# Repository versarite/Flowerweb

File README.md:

# FlowerWeb
# Written with support from ChatGPT and Claude

A small web-controlled watering system for a Raspberry Pi. Open the web page from anywhere (for example over Tailscale), watch your plants on a live camera, water them with one click, or let a timer do it every 24, 48 or 72 hours.

The server is written in Free Pascal / Lazarus and runs as a systemd service. The camera stream is served by [MediaMTX](https://github.com/bluenviron/mediamtx).

## Features

- **Manual watering:** opens the valve for a set time (1–60 s by default)
- **Automatic watering:** every 24, 48 or 72 hours. The schedule survives restarts, and a watering missed while the Pi was off runs when it comes back.
- **Live camera:** a WebRTC stream from a USB webcam or the Raspberry Pi camera
- **Status:** shows the Pi's IP address, CPU temperature, next watering time and a countdown while watering
- **Remote reboot** from the web page
- **Safe valve handling:** the valve is closed at startup, at shutdown, when the service crashes and before a reboot, and the server enforces a maximum opening time

## Hardware

| Part | Notes |
|---|---|
| Raspberry Pi | Any model with GPIO. Uses `pinctrl` (Pi 5 / Bookworm) or `raspi-gpio` (older models) |
| Relay module | Signal on **GPIO 18** by default. Active-high and active-low boards are both supported (`ActiveLow` in the ini) |
| Water valve or pump | Switched by the relay. Use a separate power supply that suits the valve |
| Camera | USB webcam (`/dev/video0`) or Raspberry Pi camera module |

A ready-made **Raspberry Pi HAT** for all of this is in [`hardware/kicad`](hardware/kicad/README.md). It has a 5 V 6 A input jack, a 24 V step-up module, a TIP121 valve driver on GPIO 18, a 24 V valve jack and a status-LED header.

> ⚠️ The relay switches the valve's supply, not mains power. If your valve or pump runs on mains voltage, use a suitably rated relay and have the wiring checked by someone qualified.

The KiCAD hat board meant as a suggestion. No frills here, only GPIO18 is connected.   

## Project layout

```
flowerweb/
├── src/        Pascal source (Lazarus project flowerweb.lpi)
│   ├── flowerweb.lpr   program start, HTTP routes
│   ├── uconfig.pas     reads/writes config/flowerweb.ini
│   ├── uRelay.pas      valve control and watering timer
│   ├── uapi.pas        REST API
│   ├── uwebfiles.pas   serves the web page
│   ├── usysinfo.pas    CPU temperature and IP address
│   └── ulog.pas        logging
├── web/        index.html, app.js, style.css
├── config/     flowerweb.ini, mediamtx.yml (USB camera), mediamtx.yml_rpicam (Pi camera)
├── systemd/    flowerweb.service, mediamtx.service
├── scripts/    deploy.sh (build and install on the Pi), reset.sh (Wi-Fi watchdog)
├── hardware/   kicad/: FlowerWeb HAT schematic, board layout and BOM (see its README)
└── docs/       notes and command reference
```

On the Pi everything lives in `/home/flowerweb`, and the compiled program goes in `/home/flowerweb/bin`.

## Installation on the Raspberry Pi

1. **Install Lazarus** (for `lazbuild`) and create the folders:

   ```bash
   sudo apt install lazarus
   sudo mkdir -p /home/flowerweb/bin
   sudo chown -R pi:pi /home/flowerweb
   ```

2. **Install MediaMTX** for the camera. Download the ARM build from the [MediaMTX releases](https://github.com/bluenviron/mediamtx/releases) and put `mediamtx` in `/home/flowerweb/bin`. Copy the config that matches your camera:

   ```bash
   cp config/mediamtx.yml        /home/flowerweb/bin/mediamtx.yml   # USB webcam (needs ffmpeg)
   # or
   cp config/mediamtx.yml_rpicam /home/flowerweb/bin/mediamtx.yml   # Pi camera module
   ```

3. **Allow the service commands without a password** (`sudo visudo -f /etc/sudoers.d/flowerweb`):

   ```
   pi ALL=(root) NOPASSWD: /usr/sbin/reboot, /usr/bin/systemctl
   ```

4. **Install the services:**

   ```bash
   sudo cp /home/flowerweb/systemd/*.service /etc/systemd/system/
   sudo systemctl daemon-reload
   sudo systemctl enable --now mediamtx flowerweb
   ```

## Building and deploying

Development happens on a PC. `scripts/deploy.sh` copies the source to the Pi over SSH, compiles it there with `lazbuild`, installs it and restarts the service:

```bash
./scripts/deploy.sh
```

Set `PI_HOST` in the script to your Pi's address. Password-free SSH login is described in `docs/`.

### Testing without touching the live system

```bash
./scripts/deploy-test.sh          # copy, compile and start a test copy on port 8081
./scripts/deploy-test.sh log      # follow its log
./scripts/deploy-test.sh stop     # stop it
```

The test copy runs from `~/flowerweb-test` on the Pi in **simulation mode**. It only logs what it would do and never switches the relay or reboots the Pi. The live service, its folder and port 8080 are left alone. An orange banner on the page shows you're on the test copy. Simulation mode can also be switched on with `Simulate=1` in the ini or `--simulate` on the command line.

The Pi's `config/flowerweb.ini` is copied only the first time. After that, deploy leaves it alone so the settings you made from the web page are kept.

## Configuration

`config/flowerweb.ini`:

| Section | Key | Default | Meaning |
|---|---|---|---|
| Server | `Name` | FlowerWeb | Title shown on the web page |
| Server | `Port` | 8080 | HTTP port |
| Relay | `Pin` | 18 | GPIO pin for the relay |
| Relay | `ActiveLow` | 0 | `1` if the relay switches on when the pin is LOW |
| Relay | `PulseTimeMS` | 5000 | Valve opening time (set from the web page) |
| Relay | `MaxPulseTimeMS` | 60000 | Longest allowed opening time |
| Relay | `TimerInterval` | 0 | Hours between automatic waterings, `0` = off (set from the web page) |
| Relay | `NextWatering` | | Written by FlowerWeb. Next scheduled watering |
| Camera | `Name` / `Port` | cam / 8889 | MediaMTX path and WebRTC port |
| Logging | `Level` | INFO | `INFO` or `ERROR` |

Logs are written to `/home/flowerweb/logs/flowerweb.log`, which rolls over at 1 MB.

## Remote access

FlowerWeb has **no login**, so anyone who can reach port 8080 can water the plants and reboot the Pi. Keep it on your local network and reach it from outside through a VPN such as [Tailscale](https://tailscale.com). Don't forward the port to the internet.

Then open `http://<pi-address>:8080` in a browser.

## API

| Method | Path | Body | Description |
|---|---|---|---|
| GET | `/api/status` | | Status JSON (IP, temperature, timer, watering state, …) |
| POST | `/api/trigger` | `{"pulseTimeMS": 5000}` (optional) | Start watering. Returns `409` if already watering |
| POST | `/api/timer` | `{"timerInterval": 24}` | Set the automatic interval in hours (`0` = off) |
| POST | `/api/reboot` | | Close the valve and reboot the Pi |

Close the valve by hand at any time:

```bash
/home/flowerweb/bin/flowerweb --relay-off
```

## License

FlowerWeb is released under the [PolyForm Noncommercial License 1.0.0](LICENSE.md). You're free to use, study, change and share it for any **non-commercial** purpose: personal projects, hobby use, education, research, and charitable or public organisations. Commercial use is not permitted without the author's permission.

Copyright (c) 2026 DL1BWA

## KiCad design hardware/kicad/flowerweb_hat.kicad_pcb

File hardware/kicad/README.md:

# FlowerWeb HAT (KiCad)

A Raspberry Pi HAT (65 × 56.5 mm, 2 layers) that powers the Pi from a 5 V barrel jack and switches a 24 V valve from GPIO18.

## Files

| File | What it is |
|---|---|
| `flowerweb_hat.kicad_pro` | KiCad project. Open this one |
| `flowerweb_hat.kicad_sch` | Schematic (also as `schematic.pdf`) |
| `flowerweb_hat.kicad_pcb` | Board layout |
| `flowerweb.kicad_sym`, `flowerweb.pretty/` | Project symbol and footprint library (MT3608 module footprint) |
| `BOM.csv` | Parts list |
| `preview_*.png` | Rendered previews |

Written in KiCad 7 format, so it opens in KiCad 7, 8 and 9. All other footprints come from the standard KiCad libraries.

## Circuit

- **5 V input (J1):** PJ-063AH jack (5.5 × 2.1 mm, rated 8 A) → F1 6 A resettable fuse → +5V. D1 (1.5KE6V8A TVS) clamps overvoltage and conducts if the plug is reversed, which trips F1. C1 470 µF is bulk capacitance.
- **Raspberry Pi (J3):** 2 × 20 socket on the **bottom** side. +5V goes to pins 2 and 4 (the Pi is back-powered through the header), GND to all eight ground pins.
- **24 V (U1):** MT3608 step-up module, 5 V → 24 V, with C2 100 µF / 35 V on the output.
- **Valve driver:** GPIO18 (pin 12) → R1 1 kΩ → TIP121 base. R2 10 kΩ pulls the base low so the valve stays shut while the Pi boots. The TIP121 switches the low side of the valve, and D2 (1N4007) absorbs the coil's turn-off spike.
- **Valve jack (J2):** PJ-063AH. Centre pin = **+24 V**, sleeve = **switched side**. The sleeve is *not* ground, so don't connect it to anything else.
- **Status LED (J4):** 3.3 V (pin 17) → R3 220 Ω → header pin 1 (LED +). Pin 2 = LED −. That's about 6 mA for a red or green LED. Use a lower value (e.g. 68 Ω) for blue or white.

## Before ordering

1. Open `flowerweb_hat.kicad_pro` in KiCad.
2. In the PCB editor press **B** (Fill all zones). The copper pours are saved unfilled. Every connection, GND and 5V included, is also made by traces, so there are no ratsnest lines even before filling. The pours add copper area for the 5 A current, so always fill them before ordering.
3. Run **Inspect → Design Rules Checker** and, in the schematic, **Inspect → Electrical Rules Checker**. The board was checked with independent clearance, pour and connectivity checks while it was being made, but it has not yet been opened in KiCad itself. Run both checks once before ordering.
4. Optional: **Tools → Update Footprints from Library** adds the 3D models for the 3D viewer. Afterwards, check that J3's pin 1 is still next to mounting hole H1.
5. Plot Gerbers and drill files (**File → Fabrication Outputs**). The board uses standard rules (0.2 mm clearance, 0.3 mm tracks, 0.4 mm vias) that every PCB fab supports. The MT3608 pads have **slotted holes**, which most fabs (JLCPCB, PCBWay, Aisler) make at no extra cost.

## Assembly notes

- **Set the MT3608 to 24.0 V before soldering it in.** Feed it 5 V, turn the trimmer and measure. The TIP121 drops about 1 V, so the valve sees roughly 23 V. Set 25 V if your valve needs the full 24.
- MT3608 modules differ slightly between sellers. Line up the **IN+ / IN− / OUT+ / OUT−** marks on the PCB with the ones on the module. The slotted pads allow about ±1 mm. Solder the module on with short wire legs (cut resistor leads work).
- Solder the 2 × 20 socket on the **bottom** side. Mount the HAT with M2.5 standoffs. The usual height is 11–12 mm, but measure yours with the socket plugged in.
- Raspberry Pi 5: add `usb_max_current_enable=1` to `/boot/firmware/config.txt`. Otherwise the Pi 5 limits USB current when it's powered through the GPIO header.
- The TIP121 needs no heatsink at 150 mA (about 0.15 W).
- No ID EEPROM and no camera/display cable slot are included.

## License

PolyForm Noncommercial 1.0.0. See `LICENSE.md` in the project root.
Copyright DL1BWA 2026

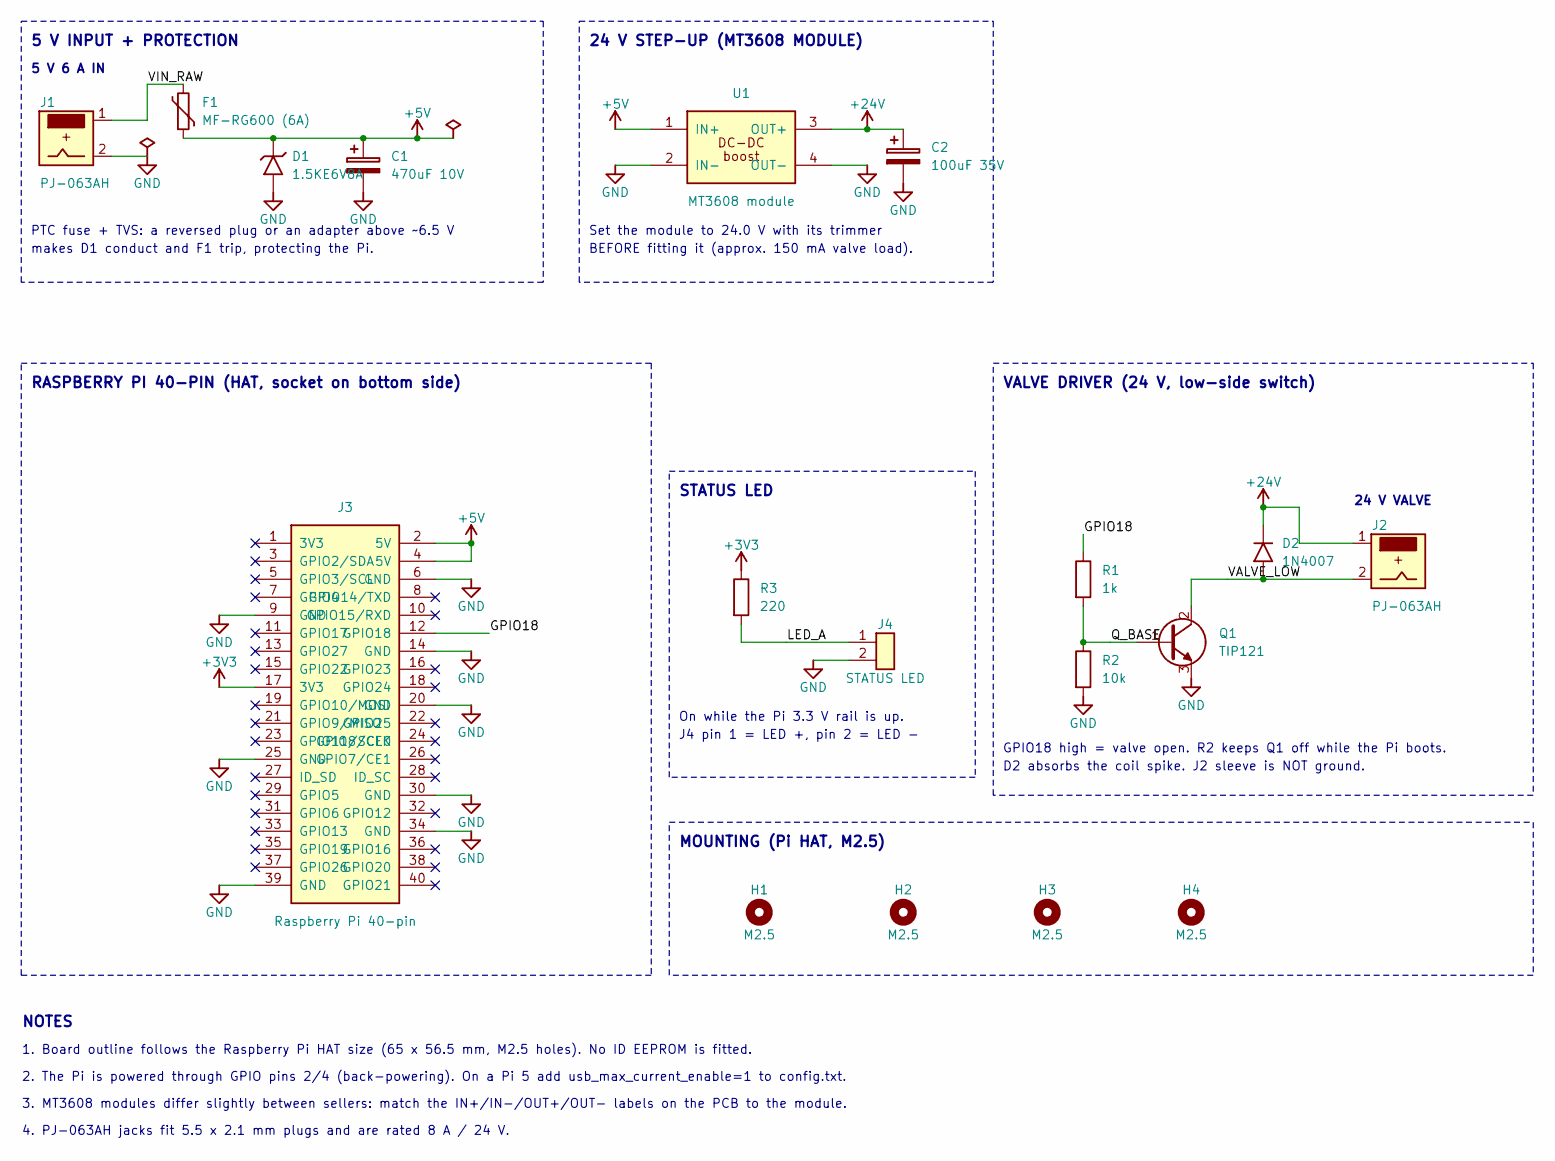
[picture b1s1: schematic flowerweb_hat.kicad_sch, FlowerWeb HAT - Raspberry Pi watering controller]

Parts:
C1: 470uF 10V; CP_Radial_D10.0mm_P5.00mm
C2: 100uF 35V; CP_Radial_D8.0mm_P3.50mm
D1: 1.5KE6V8A; D_DO-201AE_P15.24mm_Horizontal; MPN 1.5KE6V8A
D2: 1N4007; D_DO-41_SOD81_P10.16mm_Horizontal; MPN 1N4007
F1: MF-RG600 (6A); Fuse_Bourns_MF-RG600; MPN Bourns MF-RG600
H1, H2, H3, H4: M2.5; MountingHole_2.7mm_M2.5
J1, J2: PJ-063AH; BarrelJack_CUI_PJ-063AH_Horizontal; MPN CUI/Same Sky PJ-063AH
J3: Raspberry Pi 40-pin; PinSocket_2x20_P2.54mm_Vertical; MPN 2x20 female header 2.54 mm (8.5 mm)
J4: STATUS LED; PinHeader_1x02_P2.54mm_Vertical; MPN 1x2 pin header 2.54 mm
Q1: TIP121; TO-220-3_Vertical; MPN TIP121
R1: 1k; R_Axial_DIN0207_L6.3mm_D2.5mm_P7.62mm_Horizontal
R2: 10k; R_Axial_DIN0207_L6.3mm_D2.5mm_P7.62mm_Horizontal
R3: 220; R_Axial_DIN0207_L6.3mm_D2.5mm_P7.62mm_Horizontal
U1: MT3608 module; MT3608_Module; MPN MT3608 DC-DC step-up module

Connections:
+3V3: J3.17 (3V3), R3.1
+5V: C1.1, D1.1 (K), F1.2, J3.2 (5V), J3.4 (5V), U1.1 (IN+)
+24V: C2.1, D2.1 (K), J2.1, U1.3 (OUT+)
/GPIO18: J3.12 (GPIO18), R1.1
/LED_A: J4.1, R3.2
/Q_BASE: Q1.1 (B), R1.2, R2.1
/VALVE_LOW: D2.2 (A), J2.2, Q1.2 (C)
/VIN_RAW: F1.1, J1.1
GND: C1.2, C2.2, D1.2 (A), J1.2, J3.6 (GND), J3.9 (GND), J3.14 (GND), J3.20 (GND), J3.25 (GND), J3.30 (GND), J3.34 (GND), J3.39 (GND), J4.2, Q1.3 (E), R2.2, U1.2 (IN-), U1.4 (OUT-)

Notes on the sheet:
5 V INPUT + PROTECTION
5 V 6 A IN
PTC fuse + TVS: a reversed plug or an adapter above ~6.5 V
makes D1 conduct and F1 trip, protecting the Pi.
24 V STEP-UP (MT3608 MODULE)
Set the module to 24.0 V with its trimmer
BEFORE fitting it (approx. 150 mA valve load).
RASPBERRY PI 40-PIN (HAT, socket on bottom side)
VALVE DRIVER (24 V, low-side switch)
24 V VALVE
GPIO18 high = valve open. R2 keeps Q1 off while the Pi boots.
D2 absorbs the coil spike. J2 sleeve is NOT ground.
STATUS LED
On while the Pi 3.3 V rail is up.
J4 pin 1 = LED +, pin 2 = LED -
MOUNTING (Pi HAT, M2.5)
NOTES
1. Board outline follows the Raspberry Pi HAT size (65 x 56.5 mm, M2.5 holes). No ID EEPROM is fitted.
2. The Pi is powered through GPIO pins 2/4 (back-powering). On a Pi 5 add usb_max_current_enable=1 to config.txt.
3. MT3608 modules differ slightly between sellers: match the IN+/IN-/OUT+/OUT- labels on the PCB to the module.
4. PJ-063AH jacks fit 5.5 x 2.1 mm plugs and are rated 8 A / 24 V.

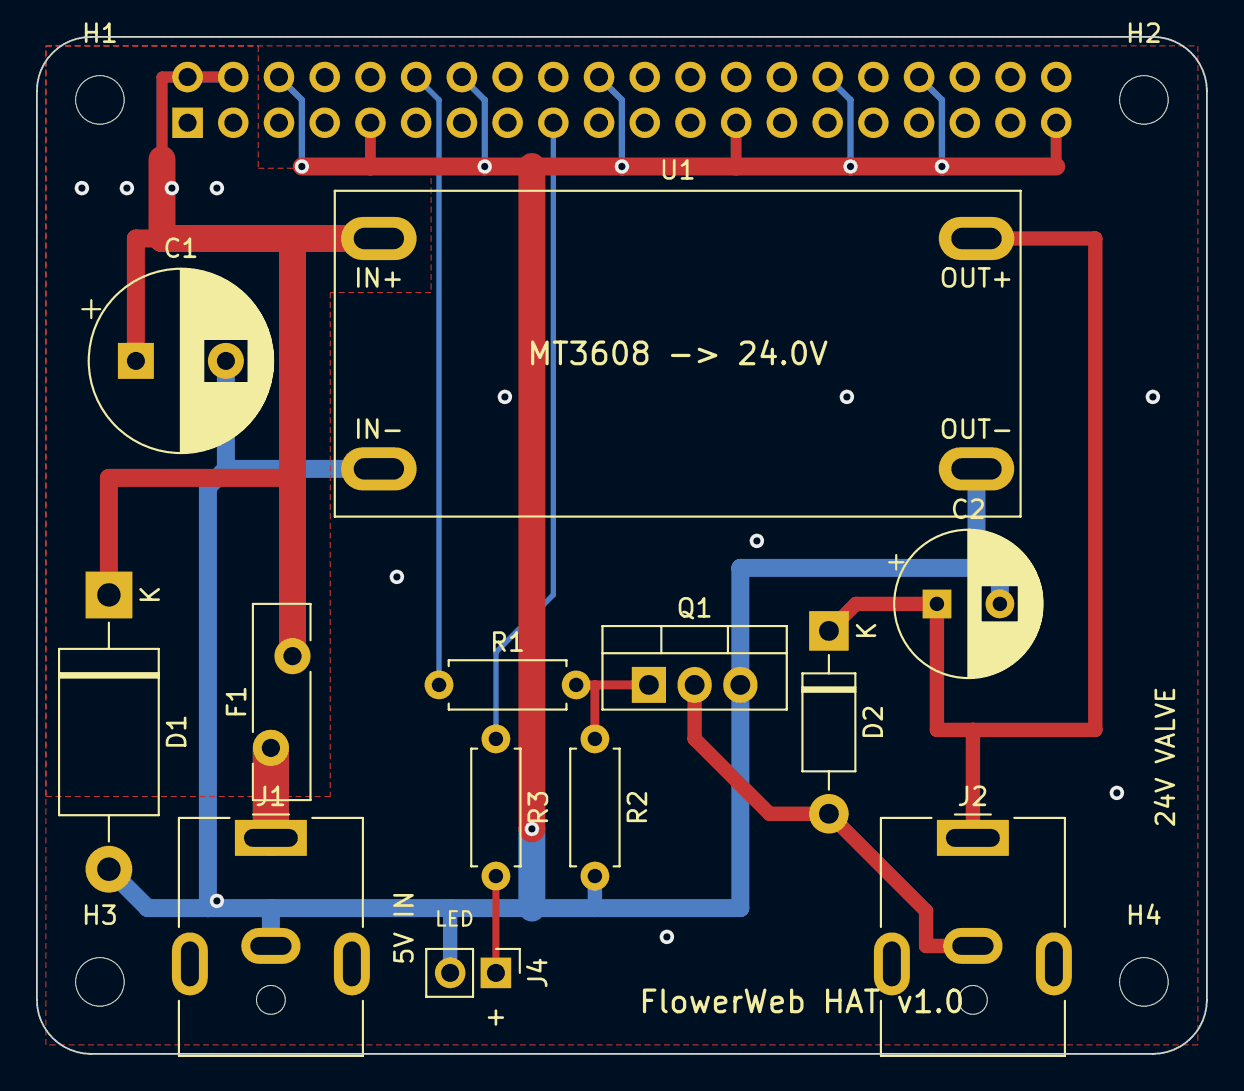
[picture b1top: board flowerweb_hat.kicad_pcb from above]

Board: 2 copper layers, 65.0 x 56.5 mm, 18 parts (1 on the bottom side), 9 nets.

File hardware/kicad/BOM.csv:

Ref,Qty,Value,Part / MPN,Description,Footprint
C1,1,470uF 10V,,"Electrolytic, 10 mm dia, 5 mm pitch, >=10 V",Capacitor_THT:CP_Radial_D10.0mm_P5.00mm
C2,1,100uF 35V,,"Electrolytic, 8 mm dia, 3.5 mm pitch, >=35 V",Capacitor_THT:CP_Radial_D8.0mm_P3.50mm
D1,1,1.5KE6V8A,1.5KE6V8A,"TVS 1500 W, 5.8 V standoff, unidirectional",Diode_THT:D_DO-201AE_P15.24mm_Horizontal
D2,1,1N4007,1N4007,Flyback diode across the valve coil,Diode_THT:D_DO-41_SOD81_P10.16mm_Horizontal
F1,1,MF-RG600 (6A),Bourns MF-RG600,"PTC resettable fuse, Ihold 6 A, 16 V",Fuse:Fuse_Bourns_MF-RG600
H1 H2 H3 H4,4,M2.5,,Pi mounting hole,MountingHole:MountingHole_2.7mm_M2.5
J1,1,PJ-063AH,CUI/Same Sky PJ-063AH,"5 V 6 A input jack, 5.5x2.1 mm, rated 8 A",Connector_BarrelJack:BarrelJack_CUI_PJ-063AH_Horizontal
J2,1,PJ-063AH,CUI/Same Sky PJ-063AH,"Centre = +24 V, sleeve = switched (NOT ground)",Connector_BarrelJack:BarrelJack_CUI_PJ-063AH_Horizontal
J3,1,Raspberry Pi 40-pin,2x20 female header 2.54 mm (8.5 mm),Mounted on the bottom side,Connector_PinSocket_2.54mm:PinSocket_2x20_P2.54mm_Vertical
J4,1,STATUS LED,1x2 pin header 2.54 mm,"Pin 1 = LED anode (+), pin 2 = cathode",Connector_PinHeader_2.54mm:PinHeader_1x02_P2.54mm_Vertical
Q1,1,TIP121,TIP121,"NPN Darlington 80 V 5 A, TO-220",Package_TO_SOT_THT:TO-220-3_Vertical
R1,1,1k,,0.25 W,Resistor_THT:R_Axial_DIN0207_L6.3mm_D2.5mm_P7.62mm_Horizontal
R2,1,10k,,"0.25 W, keeps the valve off while the Pi boots",Resistor_THT:R_Axial_DIN0207_L6.3mm_D2.5mm_P7.62mm_Horizontal
R3,1,220,,"0.25 W, LED current approx. 6 mA",Resistor_THT:R_Axial_DIN0207_L6.3mm_D2.5mm_P7.62mm_Horizontal
U1,1,MT3608 module,MT3608 DC-DC step-up module,"2 A boost module, 37x17 mm, adjust to 24.0 V",flowerweb:MT3608_Module
